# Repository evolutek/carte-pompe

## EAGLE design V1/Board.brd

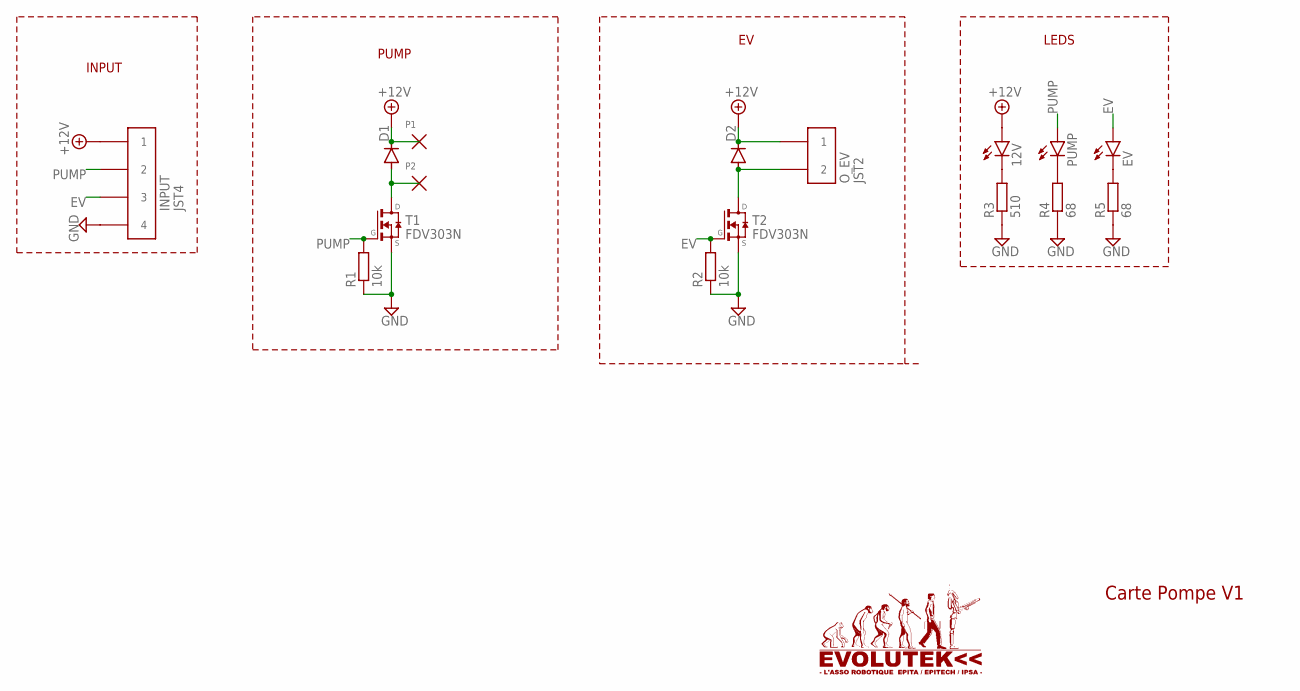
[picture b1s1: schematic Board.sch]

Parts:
12V: LEDCHIP-LED0805; CHIP-LED0805
D1, D2: DIODE-DO214AA; DO214AA
EV: LEDCHIP-LED0805; CHIP-LED0805
INPUT: JST4; B04B-PASK
O_EV: JST2; B02B-PASK
P1, P2: POWERPAD
PUMP: LEDCHIP-LED0805; CHIP-LED0805
R1, R2: 10k; R0603
R3: 510; R0603
R4, R5: 68; R0603
T1, T2: FDV303N; SOT23

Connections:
+12V: 12V.A, D1.C, D2.C, INPUT.P$1 (1), O_EV.P$1 (1), P1.P$1
EV: EV.A, INPUT.P$3 (3), R2.2, T2.1 (G)
GND: INPUT.P$4 (4), R1.1, R2.1, R3.1, R4.1, R5.1, T1.2 (S), T2.2 (S)
unnamed: D1.A, P2.P$1, T1.3 (D)
unnamed: D2.A, O_EV.P$2 (2), T2.3 (D)
unnamed: 12V.C, R3.2
unnamed: PUMP.C, R4.2
unnamed: EV.C, R5.2
PUMP: INPUT.P$2 (2), PUMP.A, R1.2, T1.1 (G)

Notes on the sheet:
INPUT
PUMP
LEDS
Carte Pompe V1

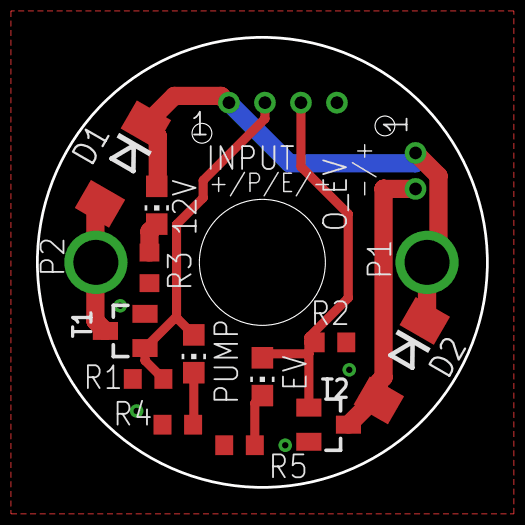
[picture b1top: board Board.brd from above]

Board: 2 copper layers, 25.0 x 25.0 mm, 16 parts (0 on the bottom side), 9 nets.

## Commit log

2019-12-14 Add a gitignore
2019-12-15 [V1] Add Lib
2019-12-15 [V1] First Version, need to check before production
2020-01-24 [V1.0] Release
2020-06-12 Add V1.1
